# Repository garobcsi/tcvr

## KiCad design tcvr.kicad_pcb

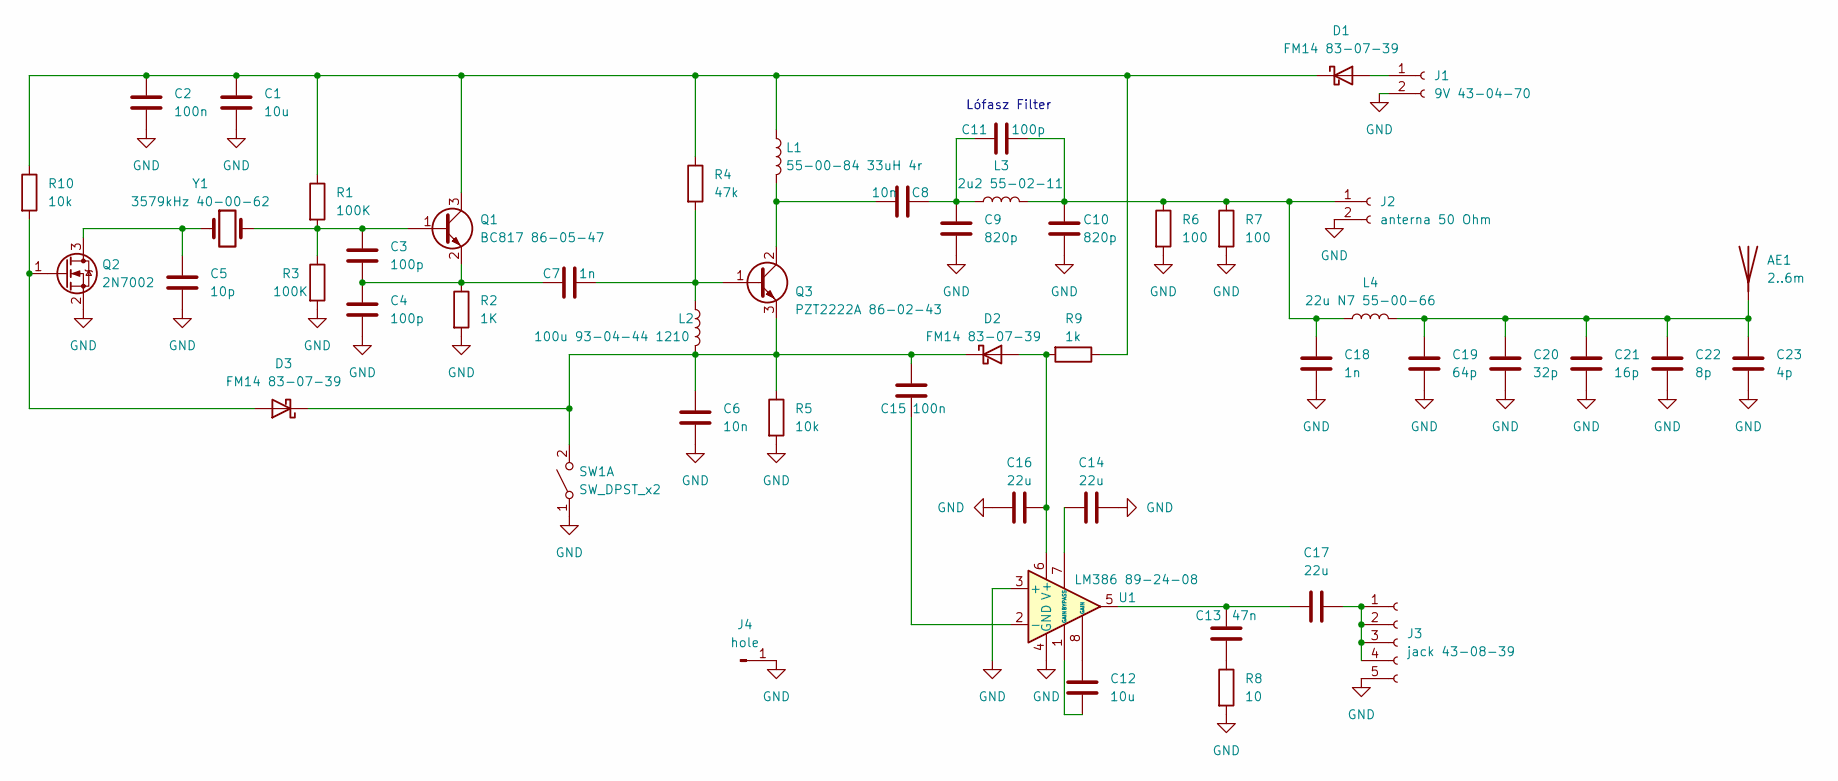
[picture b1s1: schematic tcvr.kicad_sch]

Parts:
AE1: 2..6m; PinHeader_1x01_P2.54mm_Vertical
C1, C12: 10u; C_1206_3216Metric
C2, C15: 100n; C_0805_2012Metric
C3, C4, C11: 100p; C_0805_2012Metric
C5: 10p; C_0805_2012Metric
C6, C8: 10n; C_0805_2012Metric
C7, C18: 1n; C_0805_2012Metric
C9, C10: 820p; C_0805_2012Metric
C13: 47n; C_0805_2012Metric
C14, C16, C17: 22u; C_1206_3216Metric
C19: 64p; C_0805_2012Metric
C20: 32p; C_0805_2012Metric
C21: 16p; C_0805_2012Metric
C22: 8p; C_0805_2012Metric
C23: 4p; C_0805_2012Metric
D1, D2, D3: FM14 83-07-39; D_SOD-323_HandSoldering
J1: 9V 43-04-70; PinHeader_1x02_P2.54mm_Vertical
J2: anterna 50 Ohm; coax
J3: jack 43-08-39; jack
J4: hole
L1: 55-00-84 33uH 4r; L_Axial_L9.5mm_D4.0mm_P12.70mm_Horizontal_Fastron_SMCC
L2: 100u 93-04-44 1210; L_1210_3225Metric
L3: 2u2 55-02-11; L_Axial_L9.5mm_D4.0mm_P12.70mm_Horizontal_Fastron_SMCC
L4: 22u N7 55-00-66; L_Axial_L9.5mm_D4.0mm_P12.70mm_Horizontal_Fastron_SMCC
Q1: BC817 86-05-47; SOT-23
Q2: 2N7002; SOT-23
Q3: PZT2222A 86-02-43; SOT-223-3_TabPin2
R1, R3: 100K; R_0805_2012Metric
R2: 1K; R_0805_2012Metric
R4: 47k; R_0805_2012Metric
R5, R10: 10k; R_0805_2012Metric
R6, R7: 100; R_0805_2012Metric
R8: 10; R_0805_2012Metric
R9: 1k; R_0805_2012Metric
SW1: SW_DPST_x2; key
U1: LM386 89-24-08; SOIC-8_3.9x4.9mm_P1.27mm
Y1: 3579kHz 40-00-62; Crystal_HC49-U_Horizontal

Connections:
GND: C1.2, C2.2, C4.2, C5.2, C6.2, C9.2, C10.2, C14.2, C16.2, C18.2, C19.2, C20.2, C21.2, C22.2, C23.2, J1.2, J2.2, J3.5, J4.1, Q2.2 (S), R2.2, R3.2, R5.2, R6.2, R7.2, R8.2, SW1.1 (A), U1.3 (+), U1.4 (GND)
unnamed: AE1.1 (A), C19.1, C20.1, C21.1, C22.1, C23.1, L4.2
unnamed: C8.2, C9.1, C11.1, L3.1
unnamed: C12.1, U1.8 (GAIN)
unnamed: C12.2, U1.1 (GAIN)
unnamed: C13.1, C17.1, U1.5
unnamed: C13.2, R8.1
unnamed: D1.2 (A), J1.1
unnamed: C1.1, C2.1, D1.1 (K), L1.1, Q1.3 (C), R1.1, R4.1, R9.1, R10.1
unnamed: C16.1, D2.2 (A), R9.2, U1.6 (V+)
unnamed: C6.1, C15.2, D2.1 (K), D3.1 (K), L2.2, Q3.3 (E), R5.1, SW1.2 (B)
unnamed: D3.2 (A), Q2.1 (G), R10.2
unnamed: C10.1, C11.2, C18.1, J2.1, L3.2, L4.1, R6.1, R7.1
unnamed: C17.2, J3.1, J3.2, J3.3, J3.4
unnamed: C3.1, Q1.1 (B), R1.2, R3.1, Y1.2
unnamed: C3.2, C4.1, C7.1, Q1.2 (E), R2.1
unnamed: C5.1, Q2.3 (D), Y1.1
unnamed: C7.2, L2.1, Q3.1 (B), R4.2
unnamed: C8.1, L1.2, Q3.2 (C)
unnamed: C15.1, U1.2 (-)
unnamed: C14.1, U1.7 (BYPASS)

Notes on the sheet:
Lófasz Filter

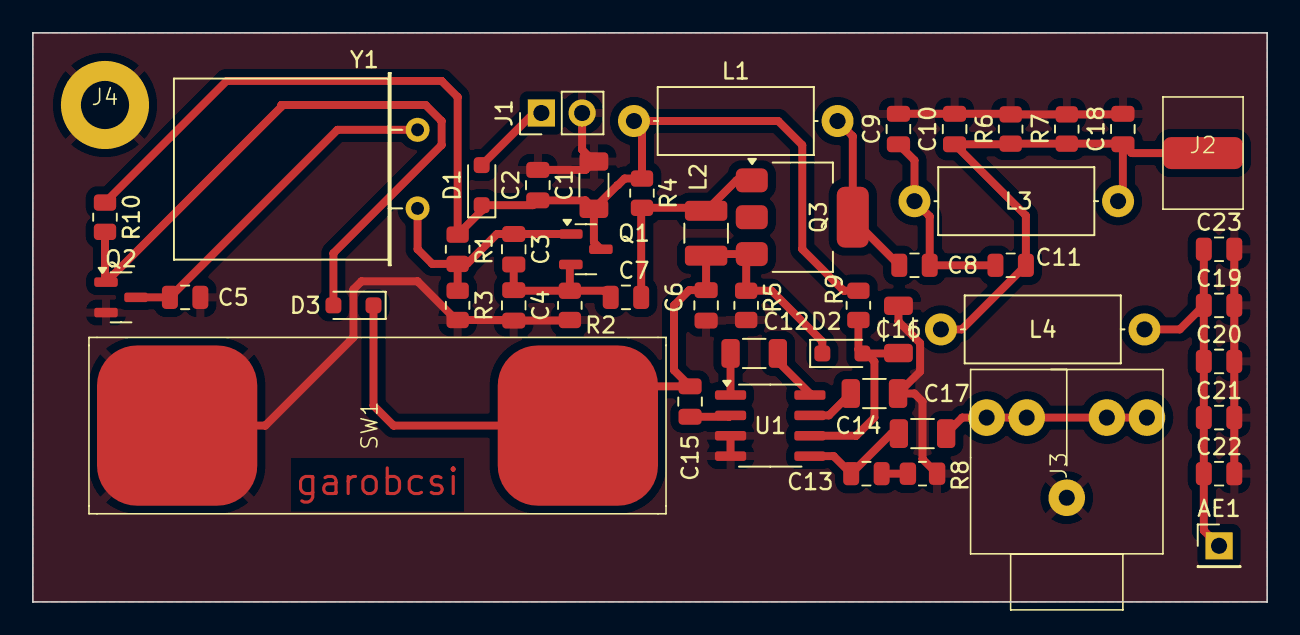
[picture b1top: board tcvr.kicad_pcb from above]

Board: 2 copper layers, 77.0 x 35.5 mm, 51 parts (0 on the bottom side), 21 nets.

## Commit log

2024-02-21 LaTeX File created
2024-02-21 added bolti megrendelési cimkék
2024-02-21 Modified sch
2024-02-23 modified LaTeX config
2024-02-28 changed schematic
2024-03-01 annotated
2024-03-01 Backup's
2024-03-01 made footprint
2024-03-01 added img and pdf's
2024-03-06 made footprint assign
2024-03-06 modified netlist
2024-03-06 updated netlist
2024-03-06 hole added
2024-03-06 backup
2024-03-06 img updated
2024-03-06 updated footprints
2024-03-06 added footprints to pcb design
2024-03-06 chenged footprint
2024-03-06 made pcb placment
2024-03-06 made pcb design
2024-03-06 pcb finished
2024-03-06 added name
2024-03-20 updated pcb
2024-03-24 added gitignore
2024-03-24 Updated to kicad 8
2024-03-24 removed backups
2024-05-14 updated tex
